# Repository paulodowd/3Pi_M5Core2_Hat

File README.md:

# 3Pi_M5Core2_Hat
simple electronic PCB to interface the Pololu 3Pi+ to the M5Stack Core2 over i2c.

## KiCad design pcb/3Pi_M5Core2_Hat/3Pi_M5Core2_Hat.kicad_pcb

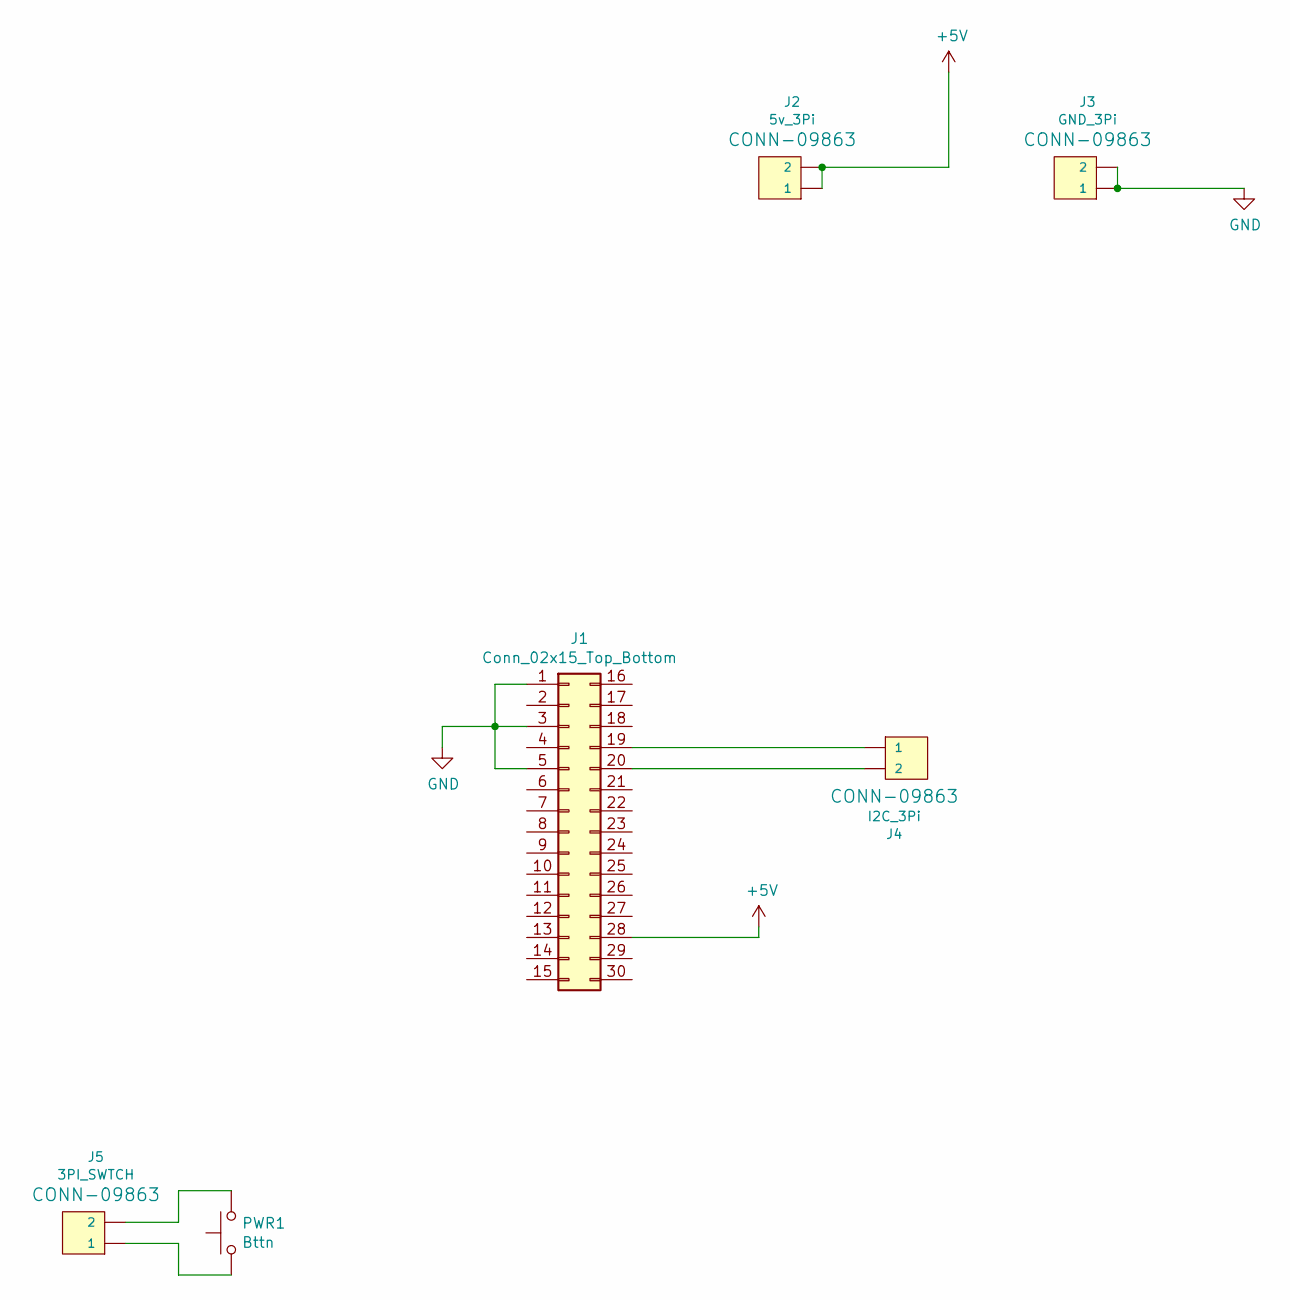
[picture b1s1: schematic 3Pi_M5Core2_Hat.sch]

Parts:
J1: Conn_02x15_Top_Bottom; PinHeader_2x15_P2.54mm_Vertical
J2: 5v_3Pi; PinHeader_1x02_P2.54mm_Vertical
J3: GND_3Pi; PinHeader_1x02_P2.54mm_Vertical
J4: I2C_3Pi; PinHeader_1x02_P2.54mm_Vertical
J5: 3PI_SWTCH; PinHeader_1x02_P2.54mm_Vertical
PWR1: Bttn; SW_PUSH_6mm

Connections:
+5V: J1.28, J2.1, J2.2
GND: J1.1, J1.3, J1.5, J3.1, J3.2
unnamed: J1.19, J4.1
unnamed: J1.20, J4.2
unnamed: J5.1, PWR1.1
unnamed: J5.2, PWR1.2

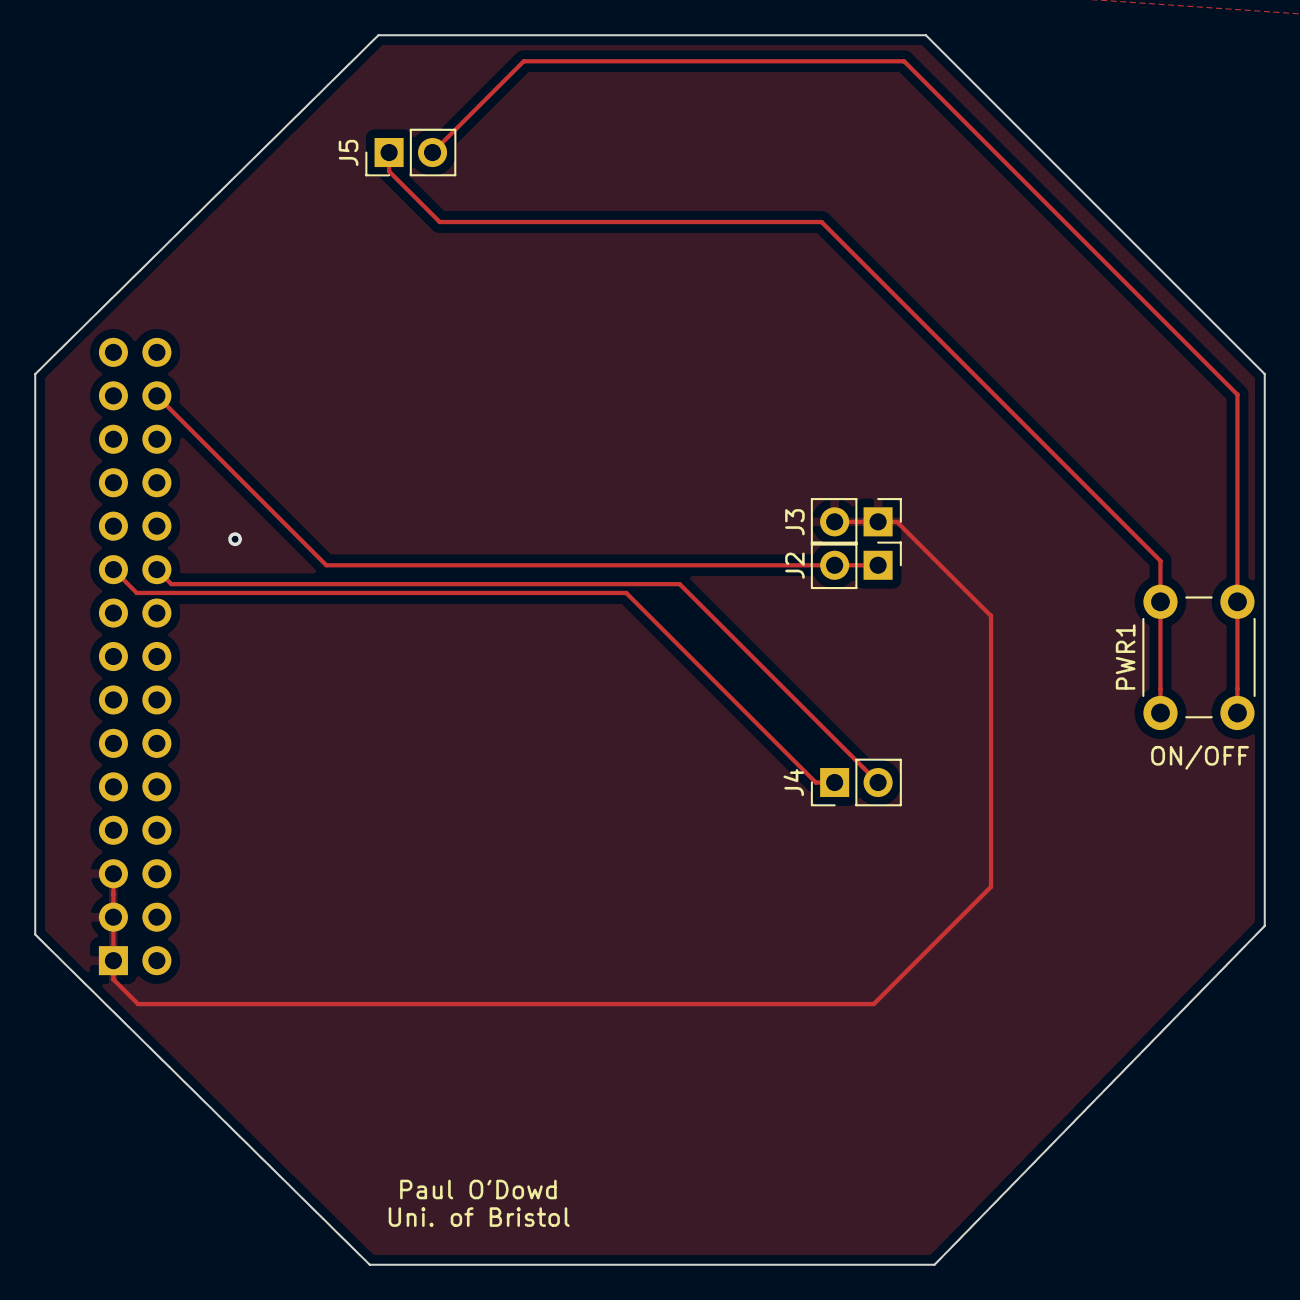
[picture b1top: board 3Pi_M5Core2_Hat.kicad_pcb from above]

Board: 2 copper layers, 71.9 x 71.9 mm, 6 parts (1 on the bottom side), 6 nets.

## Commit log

2022-07-13 PCB gerber files
